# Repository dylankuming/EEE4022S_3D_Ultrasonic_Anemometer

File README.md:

# EEE4022S 3D Ultrasonic Anemometer

This repository contains the complete development files for the **3D Ultrasonic Anemometer** project developed as part of the EEE4022S course. The goal of the project is to design, build, and test a low-cost, accurate, and reliable 3D ultrasonic anemometer using Commercial-Off-The-Shelf (COTS) components. The system measures wind data in three dimensions (X, Y, and Z) using ultrasonic transducers and provides real-time data visualisation.

## Repository Structure

This repository is organized into three main directories:

1. **Arduino_code**: Contains all the Arduino code required to interface with the ultrasonic transducers, perform wind speed and direction calculations, and handle the data acquisition process.
   - [More details can be found in the `Arduino_code/README.md`](https://github.com/dylankuming/EEE4022S_3D_Ultrasonic_Anemometer/blob/main/Arduino_code/README.md)

2. **KiCad_folders**: Includes the KiCad schematics and PCB design files for the digital and analog circuits used in the project. These files outline the hardware design and connections between components. The following KiCad folders are included:

   - **Analog Board**: Contains the PCB design for the analog circuit.
     - [More details can be found in the `Analog Board README.md`](https://github.com/dylankuming/EEE4022S_3D_Ultrasonic_Anemometer/blob/main/KiCad_folders/analog_board/README.md)

   - **2D Digital Board**: Contains the PCB design for the 2D digital circuit.
     - [More details can be found in the `2D Digital Board README.md`](https://github.com/dylankuming/EEE4022S_3D_Ultrasonic_Anemometer/tree/main/KiCad_folders/2d_digital_board#readme)

   - **3D Digital Board**: Contains the PCB design for the 3D digital circuit.
     - [More details can be found in the `3D Digital Board README.md`](https://github.com/dylankuming/EEE4022S_3D_Ultrasonic_Anemometer/blob/main/KiCad_folders/3d_digital_board/README.md)

3. **matlab_code**: This directory contains MATLAB scripts used for data visualization and further analysis of the anemometer's outputs. The scripts allow for the real-time display of wind speed and direction data.
   - [More details can be found in the `matlab_code/README.md`](https://github.com/dylankuming/EEE4022S_3D_Ultrasonic_Anemometer/blob/main/matlab_code/README.md)

## Getting Started

### Prerequisites

- Arduino IDE for uploading and running the Arduino code.
- KiCad for viewing and editing the PCB design files.
- MATLAB for running the data visualization scripts.

### Installation and Usage

1. **Arduino Code**: Navigate to the `Arduino_code` folder, open the relevant `.ino` file in the Arduino IDE, and upload it to your Arduino board.
2. **KiCad Files**: Open the KiCad project files in the `KiCad_folders` directory to explore or modify the circuit designs.
3. **MATLAB Scripts**: Run the MATLAB scripts from the `matlab_code` folder to visualize the wind data captured by the anemometer.

## License

This project is open-source, and all contributions are welcome. You are free to modify and distribute the code under the terms of the MIT license.

## Author

- **Dylan Kuming**
  - Date: October, 2024

## Acknowledgements

This project was supervised by **Dr. Stephen Paine** and completed as part of the EEE4022S course at the **University of Cape Town**.

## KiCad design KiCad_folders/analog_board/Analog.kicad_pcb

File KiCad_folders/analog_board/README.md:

# Analog Board for 3D Ultrasonic Anemometer

This folder contains the KiCad design files for the **Analog Board** used in the 3D Ultrasonic Anemometer. The Analog Board plays a crucial role in processing the ultrasonic signals received from the transducers. It is responsible for signal amplification, envelope detection, and zero-crossing detection, which are required to measure the time-of-flight (ToF) of the ultrasonic pulses.

## Features
- **Signal Amplification**: Boosts the received ultrasonic signals to detectable levels.
- **Envelope Detection**: Extracts the amplitude variations of the signals for timing analysis.
- **Zero-Crossing Detection**: Detects the zero-crossing points of the ultrasonic waves for more precise ToF measurement.
- **Temperature Compensation**: Includes a temperature sensor for compensating the speed of sound based on environmental temperature.

## Components
- Tuned amplifiers for signal conditioning.
- Envelope detectors to capture signal peaks.
- Zero-crossing detectors to mark the precise timing of signal transitions.
- Temperature sensor for environmental adjustments.

## Files in this Folder
- [Analog_Board_Schematic.sch](https://github.com/dylankuming/EEE4022S_3D_Ultrasonic_Anemometer/blob/main/KiCad_folders/analog_board/Analog.kicad_sch): The KiCad schematic of the analog board.
- [Analog_Board_PCB.kicad_pcb](https://github.com/dylankuming/EEE4022S_3D_Ultrasonic_Anemometer/blob/main/KiCad_folders/analog_board/Analog.kicad_pcb): The PCB layout for the analog board.

## Usage
1. **Open the Schematic**: Load the schematic file into KiCad to view the circuit.
2. **View or Edit the PCB**: Open the PCB layout file to review the placement and routing of components.
3. **Generate Fabrication Files**: Export the necessary Gerber files from KiCad for PCB fabrication.

## License
This project is open-source under the MIT License.

## Author

- **Dylan Kuming**
  - Date: October, 2024

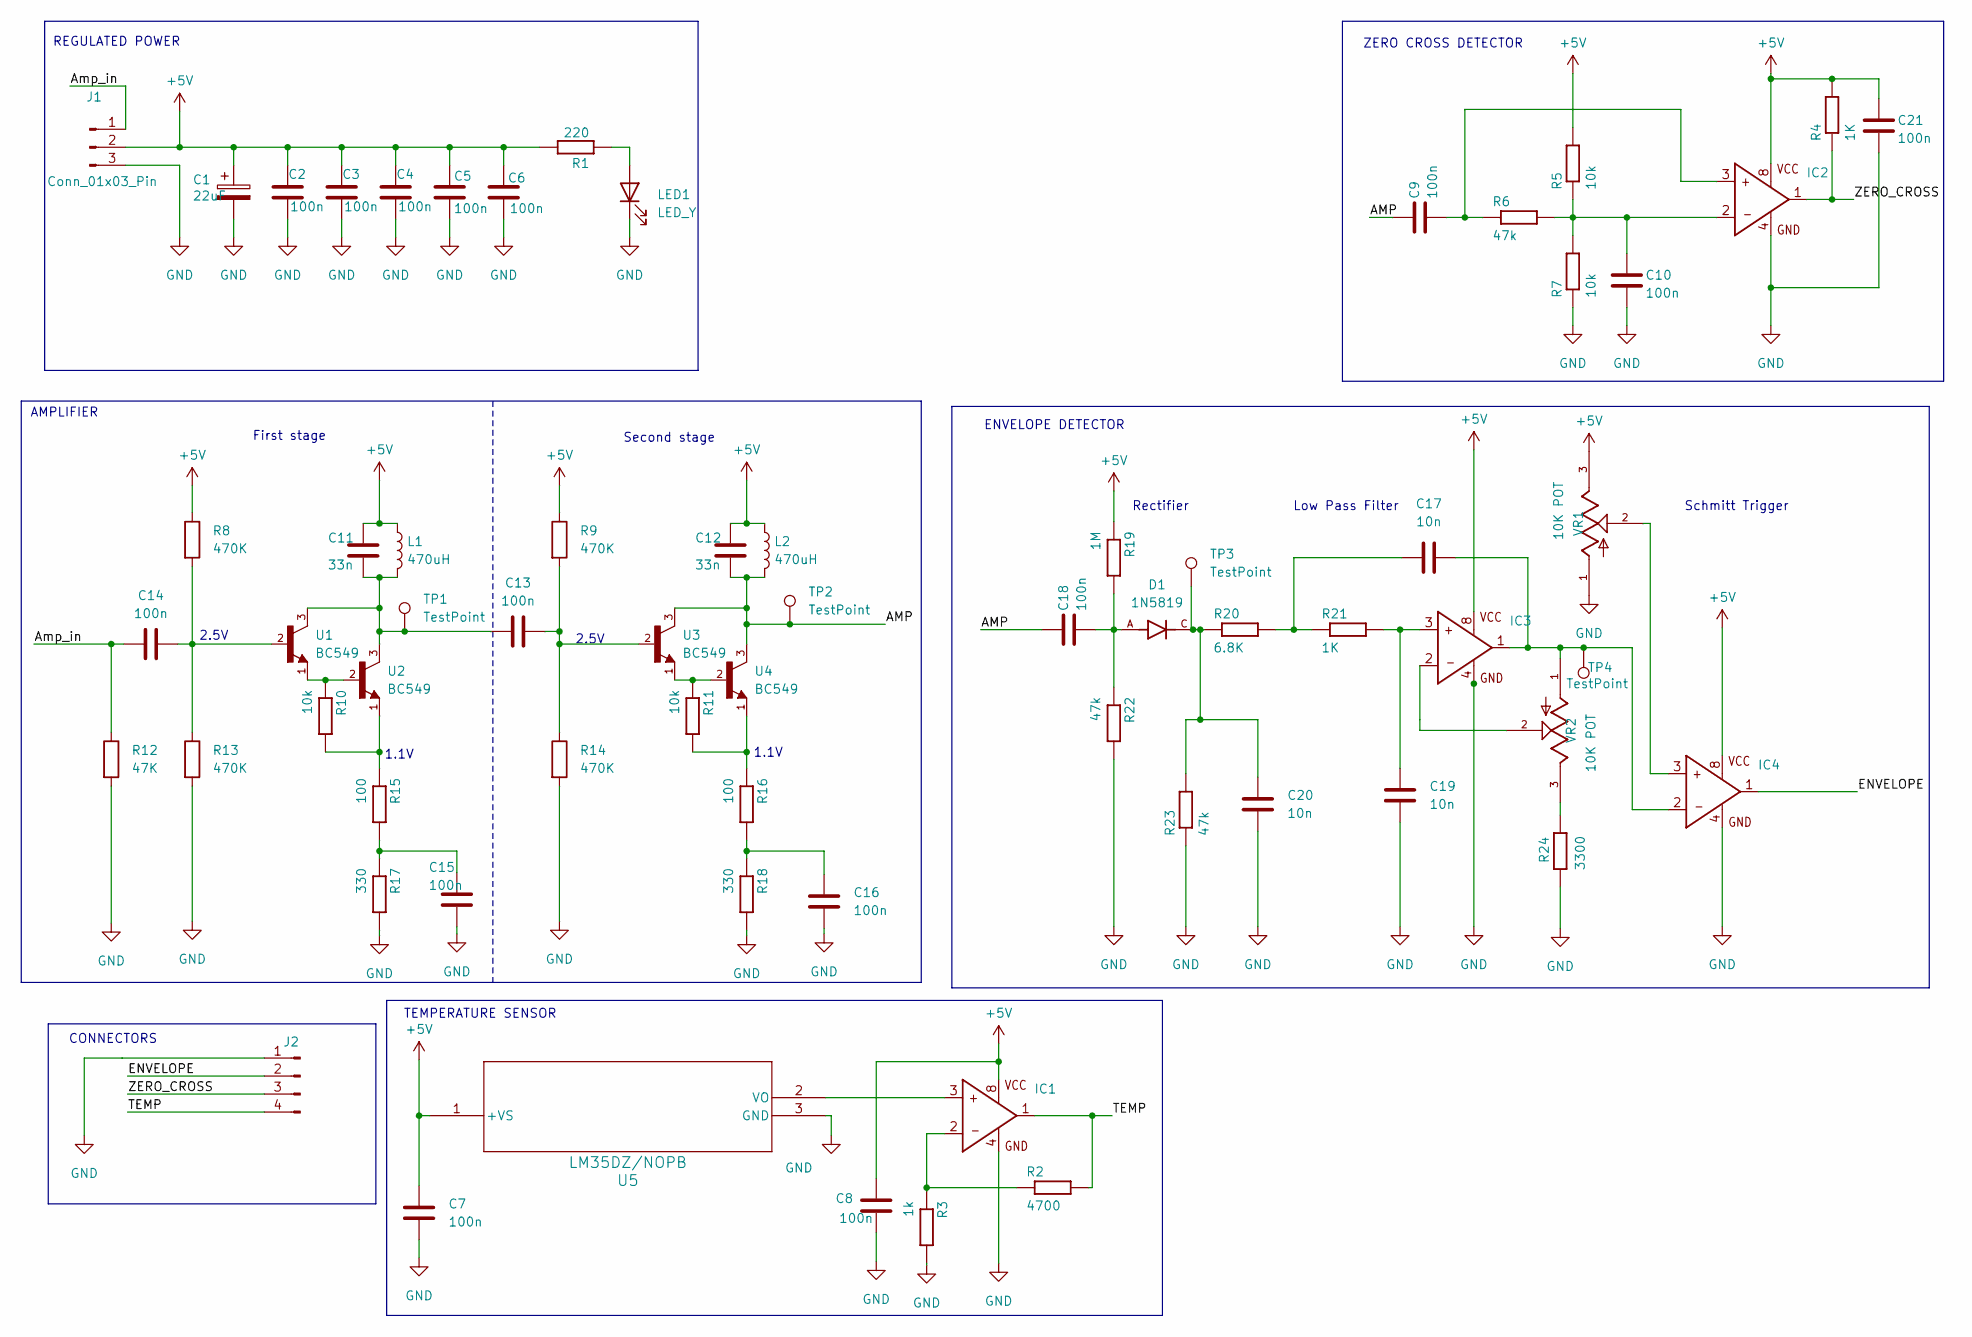
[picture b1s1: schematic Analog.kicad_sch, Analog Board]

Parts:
C1: 22uF; CP_Radial_Tantal_D10.5mm_P5.00mm
C2, C3, C4, C5, C6, C7, C8, C9, C10, C13, C14, C15, C16, C18, C21: 100n; C_0805_2012Metric
C11, C12: 33n; C_0805_2012Metric
C17, C19, C20: 10n; C_0805_2012Metric
D1: 1N5819; DIOAD1036W78L470D235; PARTREV P2104
IC1, IC3, IC4: LM358; DIP794W45P254L959H508Q8
IC2: LM393; DIP254P762X508-8
J1: Conn_01x03_Pin; PinHeader_1x03_P2.54mm_Vertical
J2: Conn_01x04_Pin; PinHeader_1x04_P2.54mm_Vertical
L1, L2: 470uH; R_Axial_Power_L20.0mm_W6.4mm_P5.08mm_Vertical
LED1: LED_Y; LED_0603_1608Metric
R1: 220; R_0805_2012Metric
R2: 4700; R_0805_2012Metric
R3: 1k; R_0805_2012Metric
R4, R21: 1K; R_0805_2012Metric
R5, R7, R10, R11: 10k; R_0805_2012Metric
R6, R22, R23: 47k; R_0805_2012Metric
R8, R9, R13, R14: 470K; R_0805_2012Metric
R12: 47K; R_0805_2012Metric
R15, R16: 100; R_0805_2012Metric
R17, R18: 330; R_0805_2012Metric
R19: 1M; R_0805_2012Metric
R20: 6.8K; R_0805_2012Metric
R24: 3300; R_0805_2012Metric
TP1, TP2, TP3, TP4: TestPoint; TestPoint_Loop_D2.50mm_Drill1.0mm
U1, U2, U3, U4: BC549; TO92
U5: LM35DZ/NOPB; Z03A
VR1, VR2: 10K POT; TRIM_3362P-1-503LF; PARTREV 08/26/10

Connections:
+5V: C1.1, C2.1, C3.1, C4.1, C5.1, C6.1, C7.1, C8.1, C11.1, C12.1, C21.1, IC1.8 (VCC), IC2.8 (VCC), IC3.8 (VCC), IC4.8 (VCC), J1.2, L1.1, L2.1, R1.2, R4.2, R5.2, R8.1, R9.1, R19.1, U5.1 (+VS), VR1.3
/AMP: C9.1, C12.2, C18.1, L2.2, TP2.1, U3.3, U4.3
/Amp_in: C14.1, J1.1, R12.1
/ENVELOPE: IC4.1 (VOUT), J2.2
/TEMP: IC1.1 (VOUT), J2.4, R2.2
/ZERO_CROSS: IC2.1 (VOUT), J2.3, R4.1
GND: C1.2, C2.2, C3.2, C4.2, C5.2, C6.2, C7.2, C8.2, C10.2, C15.2, C16.2, C19.2, C20.2, C21.2, IC1.4 (GND), IC2.4 (GND), IC3.4 (GND), IC4.4 (GND), J1.3, J2.1, LED1.1 (K), R3.2, R7.1, R12.2, R13.2, R14.2, R17.2, R18.2, R22.2, R23.1, R24.1, U5.3 (GND), VR1.1
unnamed: C11.2, C13.1, L1.2, TP1.1, U1.3, U2.3
unnamed: C13.2, R9.2, R14.1, U3.2
unnamed: C14.2, R8.2, R13.1, U1.2
unnamed: C15.1, R15.2, R17.1
unnamed: C16.1, R16.2, R18.1
unnamed: C17.1, R20.2, R21.1
unnamed: C18.2, D1.A, R19.2, R22.1
unnamed: C20.1, D1.C, R20.1, R23.2, TP3.1
unnamed: IC1.3 (VIN+), U5.2 (VO)
unnamed: IC1.2 (VIN-), R2.1, R3.1
unnamed: C9.2, IC2.3 (VIN+), R6.1
unnamed: C10.1, IC2.2 (VIN-), R5.1, R6.2, R7.2
unnamed: C19.1, IC3.3 (VIN+), R21.2
unnamed: IC3.2 (VIN-), VR2.2
unnamed: C17.2, IC3.1 (VOUT), IC4.2 (VIN-), TP4.1, VR2.1
unnamed: IC4.3 (VIN+), VR1.2
unnamed: LED1.2 (A), R1.1
unnamed: R10.1, U1.1, U2.2
unnamed: R10.2, R15.1, U2.1
unnamed: R11.1, U3.1, U4.2
unnamed: R11.2, R16.1, U4.1
unnamed: R24.2, VR2.3

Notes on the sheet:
Second stage
REGULATED POWER
ZERO CROSS DETECTOR
Low Pass Filter
First stage
TEMPERATURE SENSOR
Rectifier
1.1V
Schmitt Trigger
2.5V
CONNECTORS
AMPLIFIER
ENVELOPE DETECTOR

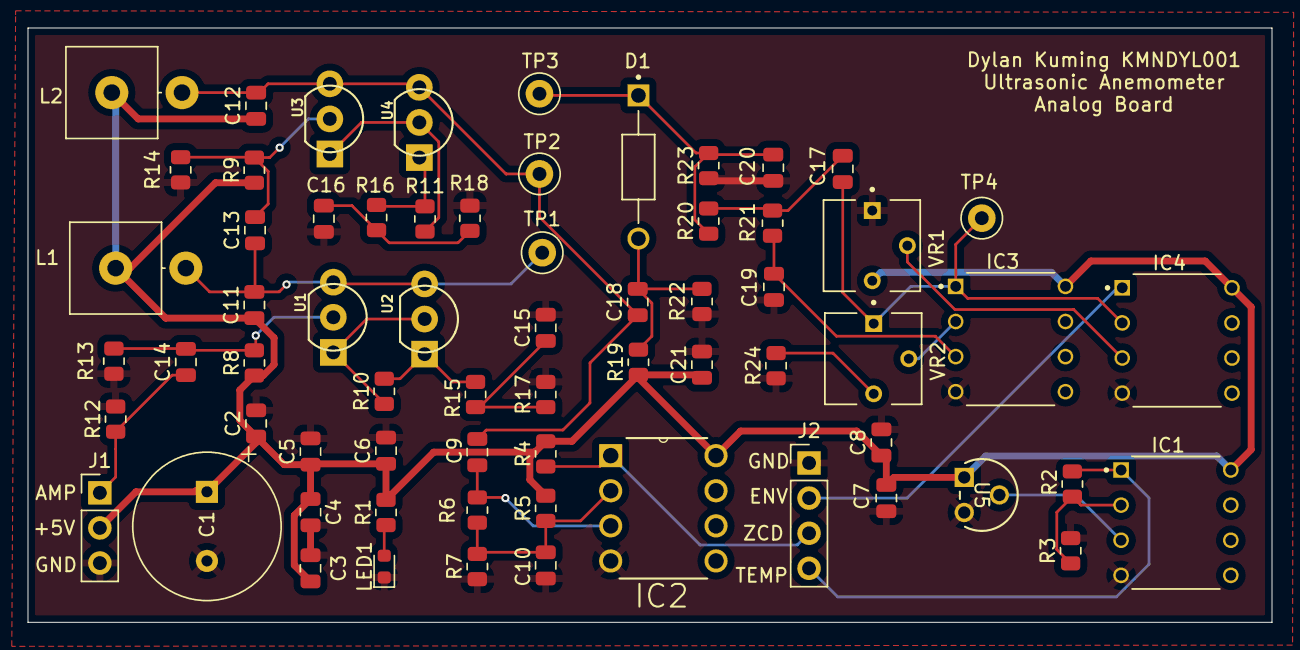
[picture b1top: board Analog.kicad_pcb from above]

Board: 2 copper layers, 90.0 x 43.0 mm, 66 parts (0 on the bottom side), 29 nets.

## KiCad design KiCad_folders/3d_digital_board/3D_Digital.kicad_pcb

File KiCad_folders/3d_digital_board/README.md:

# 3D Digital Board for 3D Ultrasonic Anemometer

This folder contains the KiCad design files for the **3D Digital Board** used in the 3D Ultrasonic Anemometer. This board expands on the 2D version by adding control for the Top-Bottom (TB) axis, allowing for full 3D wind measurement. It manages the ultrasonic transducers in the NS, EW, and TB directions and processes signals for calculating wind speed and direction in three dimensions.

## Features
- **3D Wind Measurement**: Adds the third axis (Top-Bottom) to enable full 3D wind speed and direction measurement.
- **Expanded Multiplexing**: Uses additional multiplexers to handle signals from six transducers.
- **Transducer Control**: Selects and drives the appropriate transducers for the NS, EW, and TB axes.

## Key Components
- **74HC138 3-to-8 Line Decoder**: Controls the selection of transducer pairs for the three-dimensional setup.
- **74HC4051 Multiplexer**: Routes the received signals from all six transducers to the analog board for processing.
- **Hex Inverters**: Controls the ultrasonic transducers.

## Files in this Folder
- [3D_Digital_Board_Schematic.sch](https://github.com/dylankuming/EEE4022S_3D_Ultrasonic_Anemometer/blob/main/KiCad_folders/3d_digital_board/3D_Digital.kicad_sch): The KiCad schematic of the 3D digital board.
- [3D_Digital_Board_PCB.kicad_pcb](https://github.com/dylankuming/EEE4022S_3D_Ultrasonic_Anemometer/blob/main/KiCad_folders/3d_digital_board/3D_Digital.kicad_pcb): The PCB layout for the 3D digital board.

## Usage
1. **Open the Schematic**: Use KiCad to open and modify the schematic for the 3D digital board.
2. **Edit PCB Layout**: Review the PCB layout to make any necessary adjustments.
3. **Generate Gerber Files**: Export Gerber files from KiCad for PCB fabrication.

## License
This project is open-source under the MIT License.

## Author

- **Dylan Kuming**
  - Date: October, 2024

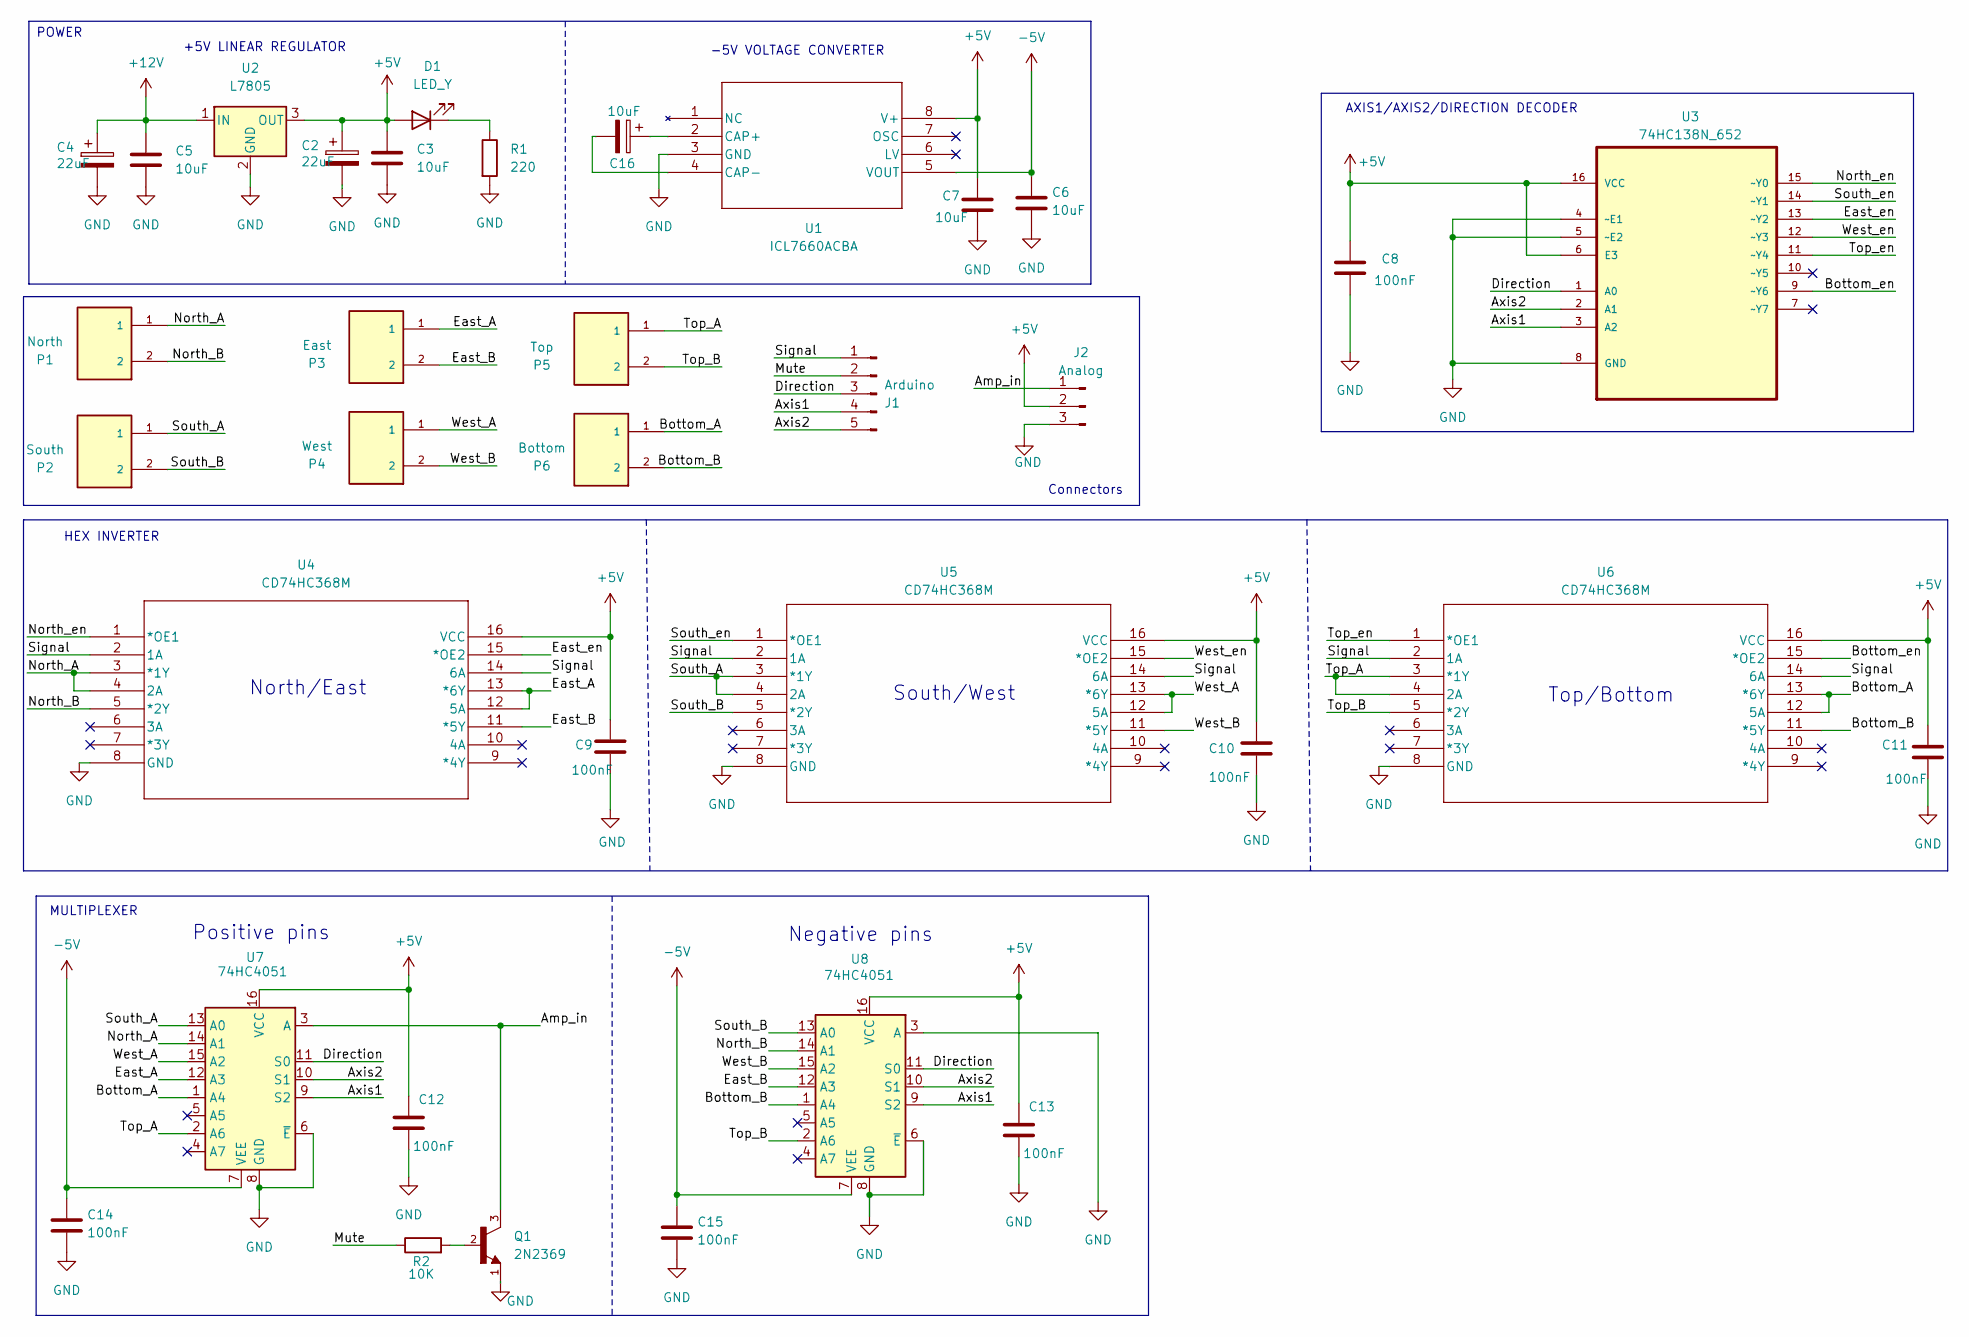
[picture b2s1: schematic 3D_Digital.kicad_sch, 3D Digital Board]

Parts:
C2, C4: 22uF; CP_Radial_Tantal_D10.5mm_P5.00mm
C3, C5, C6, C7: 10uF; C_0805_2012Metric
C8, C9, C10, C11, C12, C13, C14, C15: 100nF; C_0805_2012Metric
C16: 10uF; CP_Radial_Tantal_D4.5mm_P2.50mm
D1: LED_Y; LED_0603_1608Metric
J1: Arduino; PinHeader_1x05_P2.54mm_Vertical
J2: Analog; PinHeader_1x03_P2.54mm_Vertical
P1: North; Molex_KK-254_AE-6410-02A_1x02_P2.54mm_Vertical
P2: South; Molex_KK-254_AE-6410-02A_1x02_P2.54mm_Vertical
P3: East; Molex_KK-254_AE-6410-02A_1x02_P2.54mm_Vertical
P4: West; Molex_KK-254_AE-6410-02A_1x02_P2.54mm_Vertical
P5: Top; Molex_KK-254_AE-6410-02A_1x02_P2.54mm_Vertical
P6: Bottom; Molex_KK-254_AE-6410-02A_1x02_P2.54mm_Vertical
Q1: 2N2369; TO18
R1: 220; R_0805_2012Metric
R2: 10K; R_0805_2012Metric
U1: ICL7660ACBA; DIP794W45P254L959H508Q8
U2: L7805; TO255P1040X460X1968-3
U3: 74HC138N_652; SOT38-4_NXP; MPN 74HC138N,652
U4, U5, U6: CD74HC368M; SOT38-4_NXP
U7, U8: 74HC4051; SOT38-4_NXP

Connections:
+5V: C2.1, C3.1, C7.1, C8.1, C9.1, C10.1, C11.1, C12.1, C13.1, D1.2 (A), J2.2, U1.8 (V+), U2.3 (OUT), U3.6 (E3), U3.16 (VCC), U4.16 (VCC), U5.16 (VCC), U6.16 (VCC), U7.16 (VCC), U8.16 (VCC)
+12V: C4.1, C5.1, U2.1 (IN)
-5V: C6.1, C14.1, C15.1, U1.5 (VOUT), U7.7 (VEE), U8.7 (VEE)
/Amp_in: J2.1, Q1.3, U7.3 (A)
/Amp_off: J1.2, R2.1
/Axis1: J1.4, U3.3 (A2), U7.9 (S2), U8.9 (S2)
/Axis2: J1.5, U3.2 (A1), U7.10 (S1), U8.10 (S1)
/Bottom_A: P6.1, U6.12 (5A), U6.13 (*6Y), U7.1 (A4)
/Bottom_B: P6.2, U6.11 (*5Y), U8.1 (A4)
/Bottom_en: U3.9 (~Y6), U6.15 (*OE2)
/Direction: J1.3, U3.1 (A0), U7.11 (S0), U8.11 (S0)
/East_A: P3.1, U4.12 (5A), U4.13 (*6Y), U7.12 (A3)
/East_B: P3.2, U4.11 (*5Y), U8.12 (A3)
/East_en: U3.13 (~Y2), U4.15 (*OE2)
/North_A: P1.1, U4.3 (*1Y), U4.4 (2A), U7.14 (A1)
/North_B: P1.2, U4.5 (*2Y), U8.14 (A1)
/North_en: U3.15 (~Y0), U4.1 (*OE1)
/Signal: J1.1, U4.2 (1A), U4.14 (6A), U5.2 (1A), U5.14 (6A), U6.2 (1A), U6.14 (6A)
/South_A: P2.1, U5.3 (*1Y), U5.4 (2A), U7.13 (A0)
/South_B: P2.2, U5.5 (*2Y), U8.13 (A0)
/South_en: U3.14 (~Y1), U5.1 (*OE1)
/Top_A: P5.1, U6.3 (*1Y), U6.4 (2A), U7.2 (A6)
/Top_B: P5.2, U6.5 (*2Y), U8.2 (A6)
/Top_en: U3.11 (~Y4), U6.1 (*OE1)
/West_A: P4.1, U5.12 (5A), U5.13 (*6Y), U7.15 (A2)
/West_B: P4.2, U5.11 (*5Y), U8.15 (A2)
/West_en: U3.12 (~Y3), U5.15 (*OE2)
GND: C2.2, C3.2, C4.2, C5.2, C6.2, C7.2, C8.2, C9.2, C10.2, C11.2, C12.2, C13.2, C14.2, C15.2, J2.3, Q1.1, R1.2, U1.3 (GND), U2.2 (GND), U3.4 (~E1), U3.5 (~E2), U3.8 (GND), U4.8 (GND), U5.8 (GND), U6.8 (GND), U7.6 (~E), U7.8 (GND), U8.3 (A), U8.6 (~E), U8.8 (GND)
unnamed: D1.1 (K), R1.1
unnamed: Q1.2, R2.2
unnamed: C16.1, U1.2 (CAP+)
unnamed: C16.2, U1.4 (CAP-)

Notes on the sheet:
Negative pins
+5V LINEAR REGULATOR
Top/Bottom
Connectors
North/East
-5V VOLTAGE CONVERTER
AXIS1/AXIS2/DIRECTION DECODER
MULTIPLEXER
POWER
HEX INVERTER
Positive pins
South/West

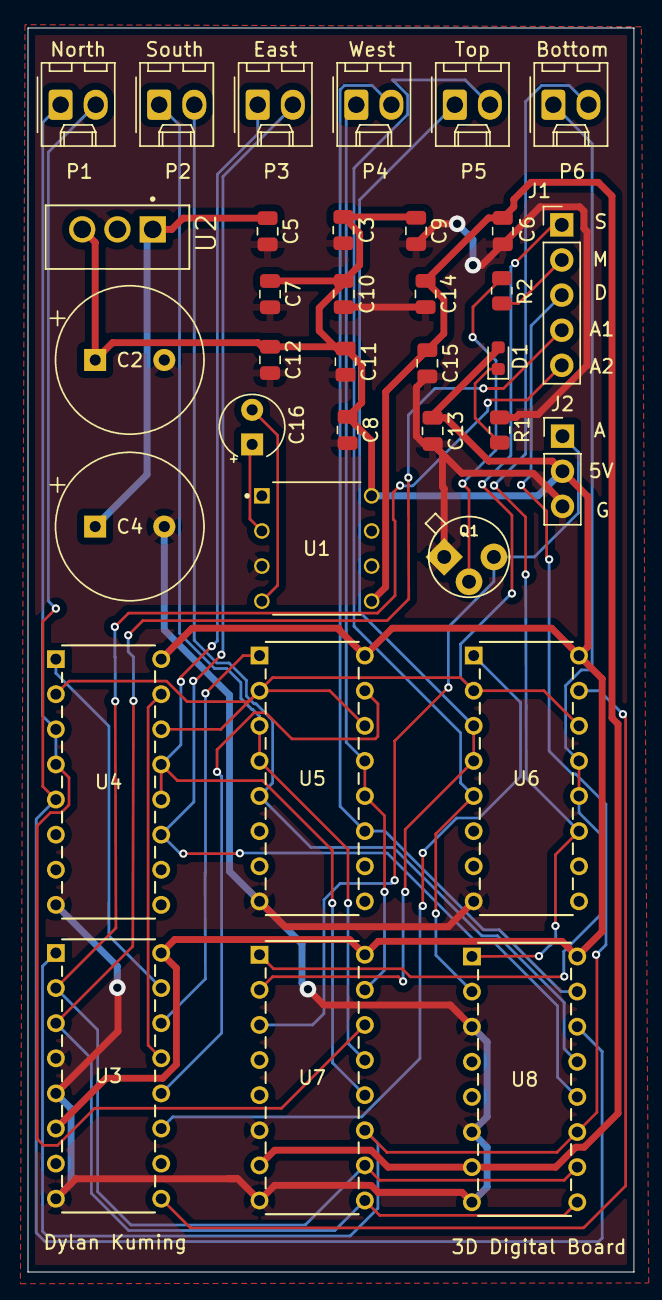
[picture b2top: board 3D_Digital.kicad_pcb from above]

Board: 2 copper layers, 43.8 x 90.0 mm, 35 parts (0 on the bottom side), 32 nets.

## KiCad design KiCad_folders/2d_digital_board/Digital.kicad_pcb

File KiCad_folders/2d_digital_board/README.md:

# 2D Digital Board for 2D Ultrasonic Anemometer

This folder contains the KiCad design files for the **2D Digital Board** used in the 2D version of the Ultrasonic Anemometer. This board is designed to control and manage the transducers along two axes: North-South (NS) and East-West (EW). It sends and receives ultrasonic pulses and calculates wind speed and direction in two dimensions.

## Features
- **Transducer Control**: Manages the transducers for both the NS and EW axes.
- **Multiplexing**: Uses multiplexers to route the signals to and from the appropriate transducers.

## Key Components
- **74HC139 Decoder**: Controls the transducer selection for NS and EW.
- **74HC368 Hex Inverters**: Drives the ultrasonic transducers.
- **74HC4052 Multiplexers**: Routes the signals to the analog board for processing.

## Files in this Folder
- [2D_Digital_Board_Schematic.sch](https://github.com/dylankuming/EEE4022S_3D_Ultrasonic_Anemometer/blob/main/KiCad_folders/2d_digital_board/Digital.kicad_sch): The KiCad schematic of the 2D digital board.
- [2D_Digital_Board_PCB.kicad_pcb](https://github.com/dylankuming/EEE4022S_3D_Ultrasonic_Anemometer/blob/main/KiCad_folders/2d_digital_board/Digital.kicad_pcb): The PCB layout for the 2D digital board.

## Usage
1. **Open the Schematic**: Load the schematic file into KiCad to view or modify the design.
2. **View or Edit the PCB**: Review the PCB layout and adjust the component placement as needed.
3. **Fabrication**: Generate Gerber files from KiCad for PCB manufacturing.

## License
This project is open-source under the MIT License.

## Author

- **Dylan Kuming**
  - Date: October, 2024

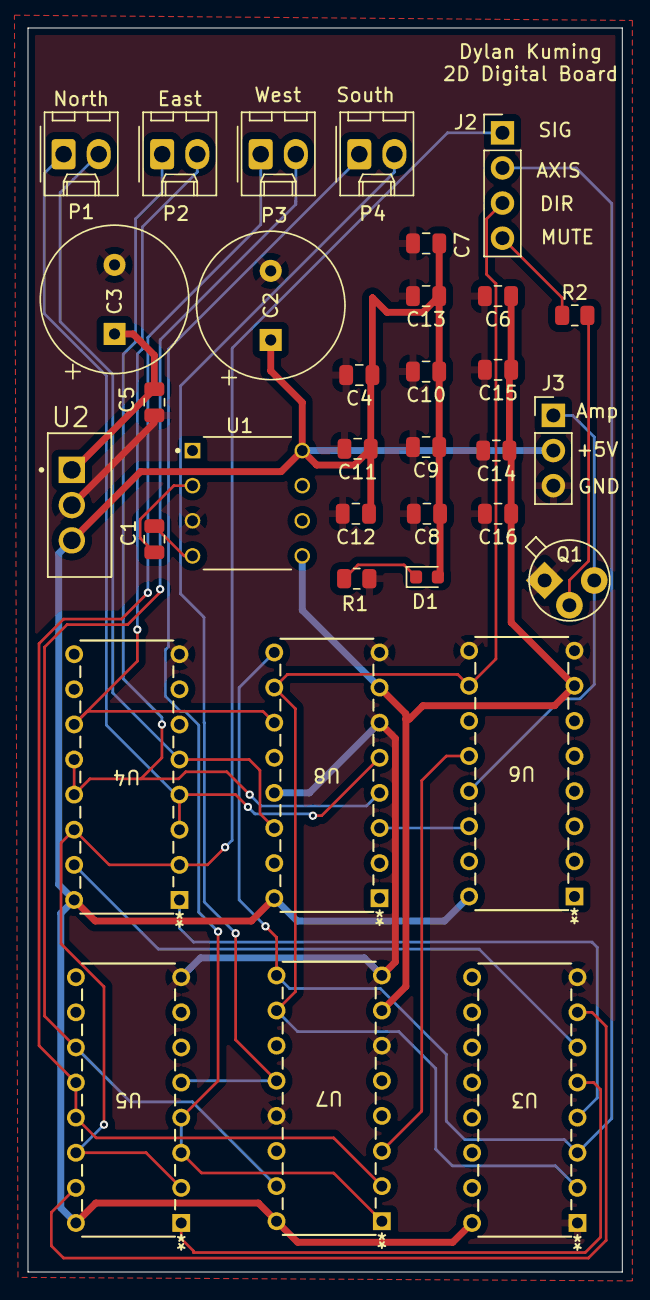
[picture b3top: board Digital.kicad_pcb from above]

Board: 2 copper layers, 43.0 x 90.0 mm, 34 parts (0 on the bottom side), 27 nets.

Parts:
C1, C4, C5, C6, C7: 10uF; C_0805_2012Metric
C2, C3: 22uF; CP_Radial_Tantal_D10.5mm_P5.00mm
C8, C9, C10, C11, C12, C13, C14, C15, C16: 100nF; C_0805_2012Metric
D1: LED_Y; LED_0603_1608Metric
J2: Arduino; PinHeader_1x04_P2.54mm_Vertical
J3: Analog; PinHeader_1x03_P2.54mm_Vertical
P1: North; Molex_KK-254_AE-6410-02A_1x02_P2.54mm_Vertical
P2: East; Molex_KK-254_AE-6410-02A_1x02_P2.54mm_Vertical
P3: West; Molex_KK-254_AE-6410-02A_1x02_P2.54mm_Vertical
P4: South; Molex_KK-254_AE-6410-02A_1x02_P2.54mm_Vertical
Q1: 2N2369; TO18
R1: 220; R_0805_2012Metric
R2: 10K; R_0805_2012Metric
U1: ICL7660ACBA; DIP794W45P254L959H508Q8
U2: L7805; TO255P1040X460X1968-3
U3: MC74HC139ADG; SOT38-4_NXP
U4, U5: CD74HC368M; SOT38-4_NXP
U6, U7, U8: MC74HC4052ADG; SOT38-4_NXP

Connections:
+5V: C2.1, C4.1, C7.1, C8.1, C9.1, C10.1, C11.1, C12.1, C13.1, D1.2 (A), J3.2, U1.8 (V+), U2.3 (OUT), U3.16 (VCC), U4.16 (VCC), U5.16 (VCC), U6.16 (VCC), U7.16 (VCC), U8.16 (VCC)
+12V: C3.1, C5.1, U2.1 (IN)
-5V: C6.1, C14.1, C15.1, C16.1, U1.5 (VOUT), U6.7 (VEE), U7.7 (VEE), U8.7 (VEE)
/Amp_in: J3.1, Q1.3, U6.13 (X)
/Amp_off: J2.4, R2.1
/Axis: J2.2, U3.3 (A1A), U7.9 (B), U8.9 (B)
/Direction: J2.3, U3.2 (A0A), U6.10 (A), U7.10 (A), U8.10 (A)
/East_A: P2.1, U4.12 (5A), U4.13 (*6Y), U8.4 (Y3)
/East_B: P2.2, U4.11 (*5Y), U8.11 (X3)
/East_en: U3.6 (Y2A), U4.15 (*OE2)
/NorthEast: U6.14 (X1), U8.3 (Y)
/North_A: P1.1, U4.3 (*1Y), U4.4 (2A), U8.5 (Y1)
/North_B: P1.2, U4.5 (*2Y), U8.14 (X1)
/North_en: U3.4 (Y0A), U4.1 (*OE1)
/Signal: J2.1, U4.2 (1A), U4.14 (6A), U5.2 (1A), U5.14 (6A)
/SouthWest: U6.12 (X0), U7.3 (Y)
/South_A: P4.1, U5.3 (*1Y), U5.4 (2A), U7.1 (Y0)
/South_B: P4.2, U5.5 (*2Y), U7.12 (X0)
/South_en: U3.5 (Y1A), U5.1 (*OE1)
/West_A: P3.1, U5.12 (5A), U5.13 (*6Y), U7.2 (Y2)
/West_B: P3.2, U5.11 (*5Y), U7.15 (X2)
/West_en: U3.7 (Y3A), U5.15 (*OE2)
GND: C2.2, C3.2, C4.2, C5.2, C6.2, C7.2, C8.2, C9.2, C10.2, C11.2, C12.2, C13.2, C14.2, C15.2, C16.2, J3.3, Q1.1, R1.2, U1.3 (GND), U2.2 (GND), U3.1 (SELECTA), U3.8 (GND), U4.8 (GND), U5.8 (GND), U6.8 (GND), U6.9 (B), U7.6 (ENABLE), U7.8 (GND), U7.13 (X), U8.6 (ENABLE), U8.8 (GND), U8.13 (X)
unnamed: D1.1 (K), R1.1
unnamed: Q1.2, R2.2
unnamed: C1.2, U1.2 (CAP+)
unnamed: C1.1, U1.4 (CAP-)

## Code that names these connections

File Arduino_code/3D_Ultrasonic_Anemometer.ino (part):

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LiquidCrystal lcd(LCD_RS, LCD_RW, LCD_EN, LCD_D4, LCD_D5, LCD_D6, LCD_D7);

// Pin definitions for the ultrasonic system
#define AXIS1 13
#define AXIS2 12
#define DIRECTION 11
#define SIGNAL 10
#define MUTE 9
#define ZEROCROSSING 8
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#define CALC 2

// Direction definitions for the axes
#define NORTH_TO_SOUTH 0 /* Axis1=L, Direction=L, Axis2=L */
#define EAST_TO_WEST 1   /* Axis1=L, Direction=L, Axis2=H */
#define SOUTH_TO_NORTH 2 /* Axis1=L, Direction=H, Axis2=L */
#define WEST_TO_EAST 3   /* Axis1=L, Direction=H, Axis2=H */
#define TOP_TO_BOTTOM 4  /* Axis1=H, Direction=L, Axis2=L */
#define BOTTOM_TO_TOP 5  /* Axis1=H, Direction=L, Axis2=H */

// Constants
#define NUMBER_OF_ROUNDS 32
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  wind_tb_total = 0;

  // Configure pins as outputs
  pinMode(AXIS1, OUTPUT);
  pinMode(AXIS2, OUTPUT);
  pinMode(DIRECTION, OUTPUT);
  pinMode(SIGNAL, OUTPUT);
  pinMode(MUTE, OUTPUT);
  pinMode(TMR1_COMPB_INT, OUTPUT);
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    case 17:
      ++axis_direction;
      if (axis_direction >= 6) {
        axis_direction = 0;  // Reset direction when all have been measured
      }

      digitalWrite(MUTE, HIGH); // Mute amplifier for the next pulse burst
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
